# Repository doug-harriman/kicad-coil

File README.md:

# kicad-coil
KiCAD Coil

See [YouTube video](https://youtu.be/UIuub70mhK0) of motor in operation.

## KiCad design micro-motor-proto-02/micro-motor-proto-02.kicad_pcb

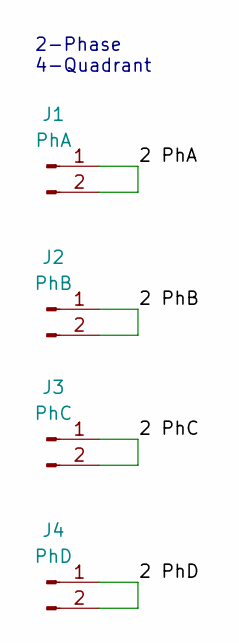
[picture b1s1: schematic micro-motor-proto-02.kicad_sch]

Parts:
J1: PhA; PinHeader_1x02_P2.54mm_Vertical
J2: PhB; PinHeader_1x02_P2.54mm_Vertical
J3: PhC; PinHeader_1x02_P2.54mm_Vertical
J4: PhD; PinHeader_1x02_P2.54mm_Vertical

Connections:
/2 PhA: J1.1, J1.2
/2 PhB: J2.1, J2.2
/2 PhC: J3.1, J3.2
/2 PhD: J4.1, J4.2

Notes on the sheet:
2-Phase 4-Quadrant

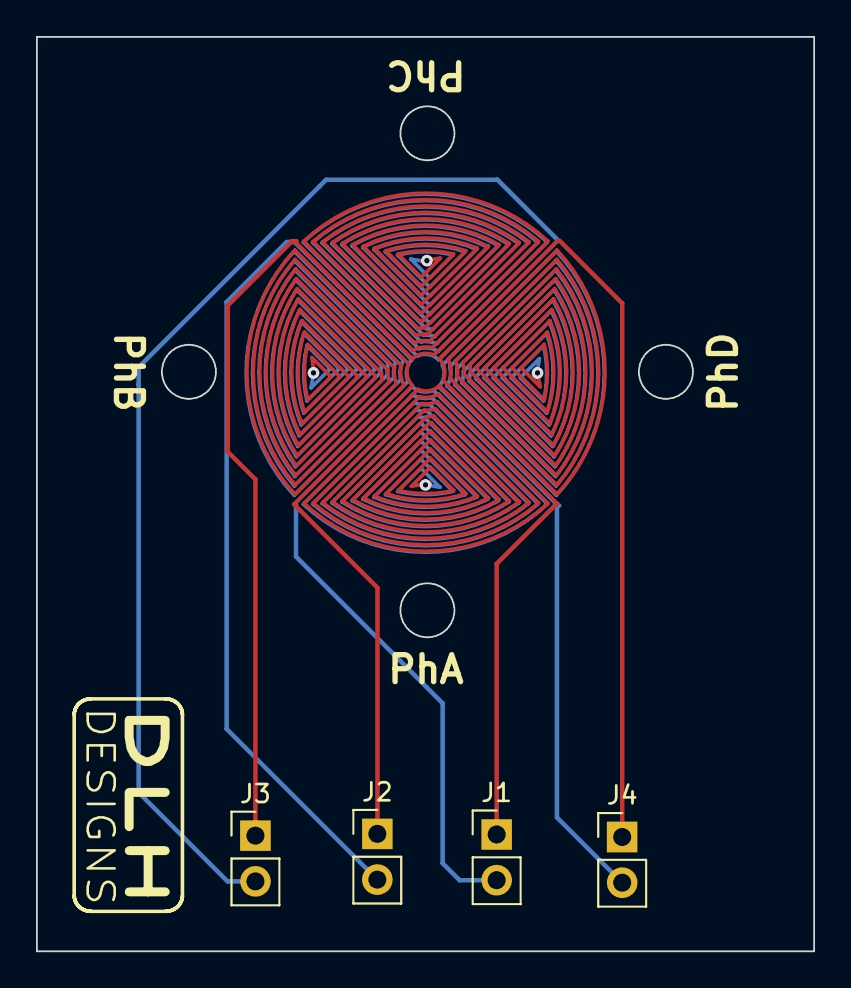
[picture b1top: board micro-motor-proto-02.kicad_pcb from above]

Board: 2 copper layers, 43.2 x 50.8 mm, 4 parts (0 on the bottom side), 4 nets.

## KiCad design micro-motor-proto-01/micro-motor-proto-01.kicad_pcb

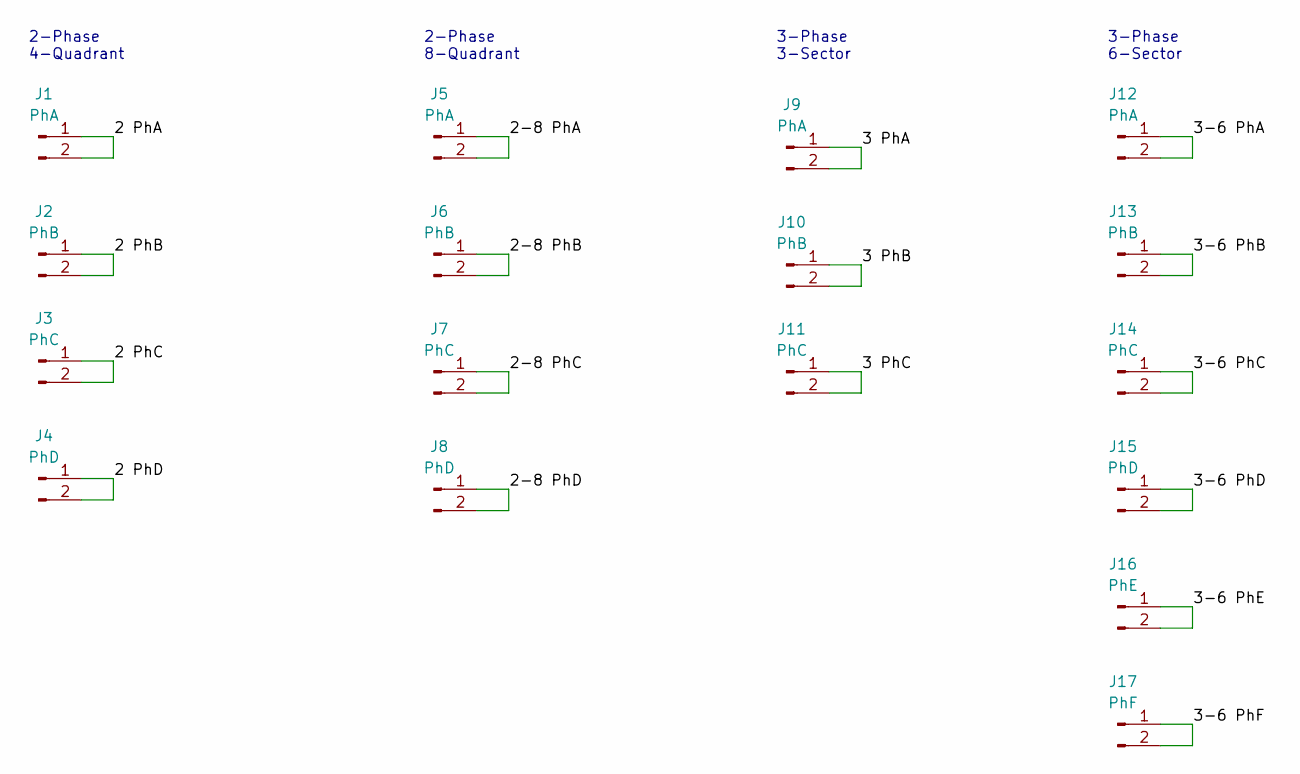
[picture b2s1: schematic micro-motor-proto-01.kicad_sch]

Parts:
J1, J5, J9, J12: PhA; PinHeader_1x02_P2.54mm_Vertical
J2, J6, J10, J13: PhB; PinHeader_1x02_P2.54mm_Vertical
J3, J7, J11, J14: PhC; PinHeader_1x02_P2.54mm_Vertical
J4, J8, J15: PhD; PinHeader_1x02_P2.54mm_Vertical
J16: PhE; PinHeader_1x02_P2.54mm_Vertical
J17: PhF; PinHeader_1x02_P2.54mm_Vertical

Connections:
/2 PhA: J1.1, J1.2
/2 PhB: J2.1, J2.2
/2 PhC: J3.1, J3.2
/2 PhD: J4.1, J4.2
/2-8 PhA: J5.1, J5.2
/2-8 PhB: J6.1, J6.2
/2-8 PhC: J7.1, J7.2
/2-8 PhD: J8.1, J8.2
/3 PhA: J9.1, J9.2
/3 PhB: J10.1, J10.2
/3 PhC: J11.1, J11.2
/3-6 PhA: J12.1, J12.2
/3-6 PhB: J13.1, J13.2
/3-6 PhC: J14.1, J14.2
/3-6 PhD: J15.1, J15.2
/3-6 PhE: J16.1, J16.2
/3-6 PhF: J17.1, J17.2

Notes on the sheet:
3-Phase 3-Sector
3-Phase 6-Sector
2-Phase 8-Quadrant
2-Phase 4-Quadrant

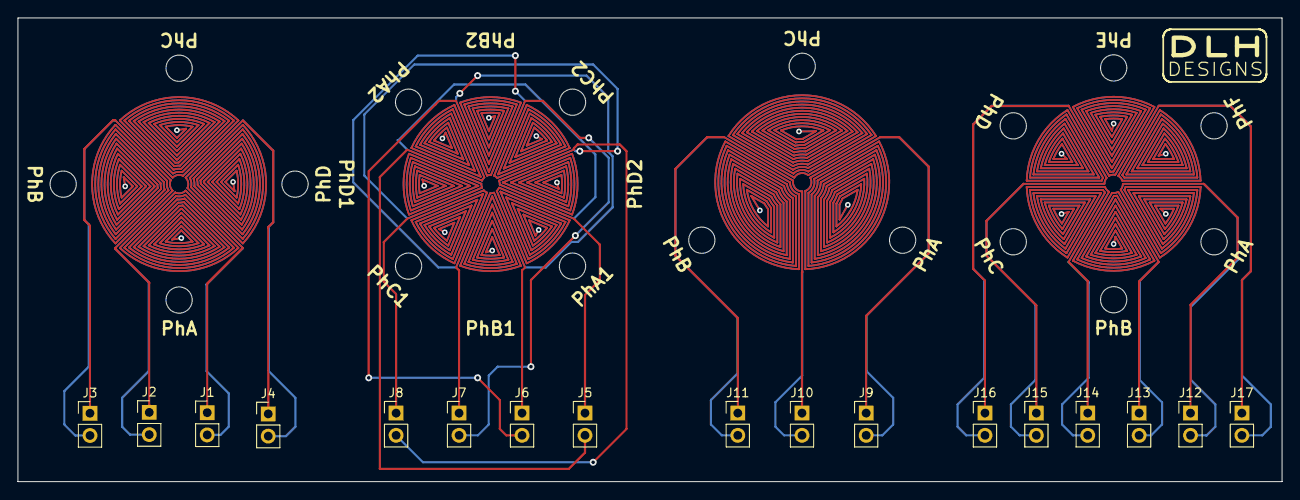
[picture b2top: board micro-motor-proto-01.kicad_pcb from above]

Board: 2 copper layers, 144.5 x 53.0 mm, 17 parts (0 on the bottom side), 17 nets.

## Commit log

2022-06-05 Initial commit.
2022-06-05 Nice arc plotting working.
2022-06-06 Segments looking correct now.
2022-06-07 Major updates to 3ph coil script.
    * Write KiCAD output
    * Translate geometry
    * Captured many TODO items.
    * Captured other URL's to important docs.
2022-06-07 Converted Segment and Arc to classes.
2022-06-08 Coil 3ph now using Track classes for generation.
2022-06-08 Major updates to class based coil generation:
    * Point
    * X & Y setters.
    * __repr__
    * Track deep copy method with new UUID for copy.
    * Segment
    * Default start/end points in constructor.
2022-06-09 Created SectorCoil class as building block. Simple 4-quadrant coil example.
    * __deepcopy__ of Groups.
    * SectorCoil is derived class from Group
    * Translate and rotate groups
2022-06-09 More class property getter/setters
2022-06-10 Multi-phase coil generator started.
    * Generic multi-phase coil implementation. Single layer working.
    * Added ability to flip sides for basic geometry
    * Many property set/get methods.
    * Fixed defect on group copy where wasn't cleaning out old elements, but re-adding.
2022-06-11 Added some setters.
    * Cleaned up some defective setter checks.
    * Cleaned up a lint warning.
2022-06-11 Added Via class.
    * __str__ for Point added
    * __repr__ for Track added
    * __repr__ for Segment and Arc updated.
    * Arc start,mid and end point accessors for 2D points.
2022-06-11 GrText class added.
    * Arc radius property accessors
    * Arc mid angle property getter.
2022-06-11 Multiphase coil labels getting added now.
2022-06-11 Segment and Arc have all property get/set methods.
2022-06-11 2 layer coil working. many small cleanups.
2022-06-11 MultiPhase coil multiplicity working.
2022-06-11 MultiPhaseCoil property get/set adds.
2022-06-12 Initial commit of info repository on KiCAD.
2022-06-12 Basic coil generation fixed so getting clean coils: ONLY for 90deg sectors right now.
2022-06-12 Basic 90 deg coil working with constraint of track width = via size.
    * Added MPC via parameter.
    * Added last half arc
2022-06-12 SectorCoil now supports arbitrary sector angles.
2022-06-13 GrCircle class added. Center & mounting holes supported.
2022-06-13 Fixed defect in Segment end point set. Also:
    * Added logging
    * Stop creating inner arcs when lines intersect.
2022-06-14 Segment intersection point now used for small, inner coils.
2022-06-14 Coil winding terminates on via size correctly now.
2022-06-15 Fixed defect where MPC vias were getting translated twice.
2022-06-15 SectorCoil pointstart/end properties.
    * MPC uses SC pointend for via placement.
2022-06-15 Group FindByClass method implemented.
2022-06-15 MPC now using Group.FindByClass method.
2022-06-15 Group FindByProperty method implemented.
2022-06-16 Cleanups.
2022-06-17 Flake8 warning cleanups.
2022-06-17 Fixed MPC variable not found error due to unhandled state.
2022-06-23 Coil point start & point end methods added. Started on new SectorCoil::Generate method.
2022-06-23 Added angle property for Segment
2022-06-26 Using correct via positions now.
    * Had been incorrectly making too many copies of elements due to a Generate() call in setting nets.
    * Missed dividing angle by 2 for bisector.
    * Had been genearing via position from the flipped via. Flipping currently swaps start/end positions so was pulling wrong position. This needs to be revisited.
2022-06-26 Coils going to correct net now.
    * SectorCoil.net setter now recursively sets net for any child Tracks.
2022-06-26 Fixed error in coil termination. Now getting max segments.
    * Moved ID & OD update points
    * Checking for termination before adding arcs.
    * Updated calc of bisector angle for via placement.
2022-06-27 Segment intersection seg generation working. Need stopping criteria.
2022-06-27 Add new Point methods
    * magniude
    * angle
    * __add__
2022-06-28 Initial PCA design commit.
2022-06-30 Added phase coil documentation.
2022-06-30 Many updates to coil generation classes:
    * Point & Segment angles handle pi to zero mapping.
    * __iadd__ and __sub__ for point
    * DistToPoint method for segment.
    * Started adding tangential direction fit calcs.
2022-06-30 KiCad notes updates.
2022-06-30 Simplified to get nets right for early dev.
2022-07-03 Via placement looks correct now for non-inner arc coils.
2022-07-10 Text pattern dia specifier. Hack around inconistencies in modulo.
2022-07-10 Multi-coil generator script.
2022-07-10 gitignore added
2022-07-10 Schematic & layout updates
2022-07-10 Ignore Kiri (KiCAD diff) files.
2022-07-10 Routing complete.
2022-12-29 Rev 2 board, swapped bottom layer coil direction.
2023-02-04 Updated documentaiton
2023-02-04 Updated params from first working test
2023-02-04 gitignore update.
2023-02-08 Added MagPyLib B-field simulation of sector coil.
2023-02-08 Removed example plots in favor of my generated plot.
2023-02-08 Added in permanent magnet.
2023-02-08 Added bottom layer coil, updated model per fab house rules.
2023-02-11 Converted config info to markdown.
2023-02-11 Added FEMM simulation
2023-02-13 Pyhon generation of FEMM geometry working.
2023-02-14 Circuit now added to coil tracks.
2023-02-20 Various documentation updates.
2023-02-20 KiCAD 6 -> KiCAD 7 conversion
2023-02-20 Formatting updates
2023-02-20 Lots of PCB design data info captured.
2023-02-20 PCB fab data update
2023-02-20 Design doc updates
2023-02-20 Rect base class & bounary_generate method for model.
2023-02-20 Base analysis now working with Python FEMM interface.
    * Magnet properties fully implemented.
    * Meshing and analysis implemeted on Femm object.
    * Magnet method for force calc working.
2023-02-21 Moving magnet analysis added to femm_model
    * GUI display control
    * B-field image generation per analysis.
    * Rect position helper properties
    * Magnet position looping added.
    * Force plot generation via Plotly & display.
2023-02-21 Added file to convert PNG's to MPG.
2023-02-21 Capture sim data to CSV.
2023-06-17 FEMM model updates captured.
2023-06-17 Added magpylib files.
2023-06-17 Added more FEMM files.
2023-06-17 Added links for PCB mfg services.
2023-06-17 Added more web links.
2023-06-17 Hall sensor field measurements.
2023-06-17 CNC shield info.
2023-06-17 Updated gitignore.
2023-06-17 Capturing info on magnetic simulation tools.
